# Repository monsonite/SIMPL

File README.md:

# SIMPL

# Introduction.

A serial, interpreted, minimal programming language - adapted for various microcontrollers including Arduino, ARM, MSP430 and experimental FPGA/simulated soft core processors.

SIMPL is intended to be a minimal, human readable scripting language based on the printable ascii character set. 

It provides a serial interface to a microcontroller using easy to remember, single character commands, and a simple interface to sent text strings and numerical output to the screen.

It can be applied to almost any cpu architecture.

# History and Inspiration

It started in 2009 when I required an interactive control method for microcontrollers from a serial terminal.

As a hardware engineer and only an occasional programmer it was driven by the underlying requirements of keeping the onchip resources to an absolute minimum and the interpreter code as simple as possible.

It began with a serial command interpreter for exercising Arduino hardware.

A single uppercase alpha character followed by a numerical parameter, allowed me to step between various routines coded into ROM. 

This was inspired the hex-monitor/debug programs of the mid-1970s to 1980s where uppercase characters followed by a 16-bit address or 8-bit data word allowed you to Examine, Modify and Run programs stored in RAM. 

WozMon on the Apple I was representative of this class of programs. 

https://steckschwein.de/2018/07/22/wozmon-a-memory-monitor-in-256-bytes/ 

A very small interpreter, few commands and tight assembley language programming allowed a useful hex editor in fewer than 256 bytes of code - fitting into a 256byte PROM on the Apple I.  

What started as a variant on a hex monitor has evolved into an interactive language toolkit for exercising a virtual machine VM.

Historical documentation can be found in my blog "Sustainable Suburbia" starting in May 2013: 

http://sustburbia.blogspot.com/2013/05/txtzyme-minimal-interpreter-and.html

At all times I apply the KISS principle - Keep it SIMPL, stupid.

# txtzyme

The breakthrough I needed for what became SIMPL was inspired by Ward Cunningham's Txtzyme nano-interpreter https://github.com/WardCunningham/Txtzyme which I first encountered in May of 2013. I combined Ward's elegant and compact nano-interpreter with my uppercase serial command interpreter.

A compact version of Ward's txtzyme that will run on an ATmega328 Arduino is located here:

https://github.com/monsonite/SIMPL/blob/master/txtzyme_1.ino

It uses 4418 bytes of flash ROM, much of which is attributed to the Arduino I/O functions. 

Many of these can be rewritten for brevity. The baudrate is 115200.

Ward had written a compact interpreter in Arduino C++ which allowed the Arduino's peripheral I/O functions to be accessed using only 13 primitive commands all operating with a 16-bit "register" x :

p print the number contained in x as a 16-bit integer

d define a digital pin

i test the digital pin for input

o set the digital pin either logic 1 or 0

m a millisecond delay

u a microsecond delay

{ start a loop

} end a loop

k read the loop counter

s sample the ADC

_ Print out the text enclosed between the underscored e.g. _Hello World_

h Print out a list of commands and basic help

v Print out the version of the mcu

An early version of Ward's Txtzyme interpreter can be seen here - only about 100 lines of C code:

https://github.com/WardCunningham/Txtzyme/blob/master/Arduinozyme/Arduinozyme.ino

It immediately became apparent that Ward had created the REPL in 2 simple routines contained within the main loop:

txtRead - If serial character present, put it into next location of a serial input buffer - until CRLF pressed

txtEval - Take character from input buffer, identify using switch-case structure and perform action. Loop back to txtRead

It was obvious that by extending the switch-case statement within txtEval, that many more commands could be added. So I added maths, logic and comparison operations and a second variable "y". For example:

123 456 + p       // Put 123 in x, 456 in y, ADD them together in x and print out x followed by a CRLF

Maths operators + - * and / and logical operations & | ^ and ~ were added at this time.

I then started thinking about conditional execution.  Ward had already provided an example of how a snippet of code would be conditionally executed depending on whether a port pin was read as 0 or 1. 

This made ingenious use of his loop structure - code enclosed between braces {........}

9{........}   Repeat the enclosed code 9 times

1{........}   Execute the enclosed code once

0{........}   Skip the enclosed code

An unexpended bonus of this was that comments could be added using a comment in braces preceded by a zero:

0{ This is a comment that will be ignored by interpreter }

Any operation that results in x being 1 or 0 can be used to determine whether the enclosed code is executed or not.

This allowed a simple mechanism for the comparison operators:

Less than <

Equal to =

Greater than >

# Extensibility

Having come from a Forth background, I was familiar how Forth can be extended with new user functions using the "Colon Definition"

Forth uses a dictionary structure and a dictionary look-up to find the location of the code to execute for a particular function. I decided that this could be massively simplified, by restricting the user to only 26 user functions, allocated to the uppercase characters A-Z.

The second big breakthrough was realising that I could point the interpreter to any address in RAM, and not just the input buffer, and have it execute the ascii-based code located there. This gave a simple mechanism for users to write their own SIMPL code into RAM.

You can effectively point the txtEval function to any buffer in memory and it will execute the virtual commands found there until it finds a CRLF.

# Other Influences      

SIMPL builds upon Ward's philosopy of keeping things simple, but adds significantly more functionality and provides the means to make a user extensible language.

SIMPL was also heavily influenced by Charles H. Moore's Forth. It uses the same reverse polish notation RPN,  placing the operands on the stack before executing the operator function.

SIMPL has it's roots in the first electronic computers of the late 1940s where the instruction set was based on uppercase alphabetic characters read from a teletype paper tape into memory. Teletype character sets were limited to uppercase alpha characters, numerals and a few punctuation symbols.

Each character was chosen to have a strong mnemonic value so that it was easily remembered, and made code listings easier to read and write - with fewer mistakes. 

See the Cambridge EDSAC from 1948 for examples of an alpha character instruction set:  https://www.cl.cam.ac.uk/~mr10/Edsac/edsacposter.pdf

SIMPL has evolved as a human readable pseudo-language to control a 16-bit virtual machine based on a Minimal Instruction Set Computer (MISC). If the interpreter is written in C it is easily extended to accommodate 32-bit words.

SIMPL performs the Read-Eval-Print Loop (REPL) required by a serial interpreter shell.  

A MISC is a computer architecture typically defined by a very small instruction set - often with only 8 to 32 instructions. 

One example is the PDP-8, a 12-bit machine from 1965 which had 8 primitive instructions plus the means to control operations on it's accumulator by directly decoding the bitfield from the instruction word. Despite the lack of instructions, the PDP-8 was a versatile machine with it's hardware deficiencies being made up for in software macros.

Additionally, new User functions can be built up by concatenating exisisting functions - this makes SIMPL extensible.

Unlike Forth, there is no dictionary and this avoids the overheads of additional parsing and dictionary searches. SIMPL can be written in about 2kbytes or less, whereas Forth may require 6k bytes. This makes it quicker and easier to port to the assembly language of an unfamiliar microcontroller.

The use of single ascii character commands means that a function can be executed with nothing more than a table look-up to obtain an execution address.

SIMPL is effectively a human readable language for implementing a 16-bit Von Neumann virtual machine on top of the native assembly language of the cpu.

It can be applied to any resource limited processor, it is easier to read and write than assembler but not as complex as a full Forth implementation. 

# Functionality.

SIMPL sets up a minimal serial shell which allows you to control a microcontroller from a few ascii characters typed from a serial terminal.

Numbers 0-9  are processed as a 16-bit integer and used as numerical input (literals) or as control parameters

lowercase alpha a-z  Usually used to access a predefined routine stored in ROM  eg. p is printnumber, u is microsecond delay

Uppercase alpha A-Z  Frequently used to define User Commands or parameters, created to meet the requirements of the application

Symbols Used for arithmetic, logic, loop control and program flow purposes.

This convention is suggested as it gives each character a strong mnemonic value and makes the code more readable. However any of the 96 printable ascii characters could be used to initiate any function in code.

Each ascii character acts as an instruction for a command, forcing a jump to a routine that executes the command, before returning to the interpreter to process the next serial character.

The code required to do this is very straightforward and can be implemented as a large switch-case statement or look up table contained within a while loop.

The serial interpreter was first conceived as a means to access and control the Arduino language functions from a serial link, such as digitalWrite, digitalRead, analog, delay, delaymicroseconds, serialPrint etc.

Later arithmetic, logical, looping and program flow operations were added to extend the functionality.

I describe it as a toolkit, because it has the means to customise it to your own application. Every ascii character, except numerals is treated as a bytecode command. Numeric strings are converted into 16-bit intergers and placed on the stack. They are used as parameters to control the operation of the command.  

For example 1000m will invoke a delay of 1000 milliseconds - ideal for timing operations, flashing LEDs, generating audio tones etc.

SIMPL appears as a series of short ascii phrases For example:

Make a LED on pin 13 flash 10 times, 100mS on and 1000mS off - just 20 characters terminated by a CRLF

13d10{1o100m0o1000m}

13d  - select digital pin 13

10{  - set the loop counter to 10 and begin the loop

1o   - output 1 (HIGH) to the selected pin

100m - delay for 100 milliseconds

0o   - output 0 (LOW) to the pin

1000m  delay for 1000 milliseconds

}    - loop back to the beginning until the loop counter = 0

If you want to keep this code snippet, you can allocate it to a User Command, normally an uppercase character A-Z. Here we use F for flash

:F13d10{1o100m0o1000m}

Every time you type F the mcu will flash the LED 10 times. The code behind F can be redefined at any time to change the flash behaviour

FFFF will execute the code 4 times - flashing the LED 40 times.

# Further Thoughts

SIMPL code is very compact. A lot can be performed using short snippets, taking up very small memory resources. It is the equivalent of a programming "Shorthand" - designed to be quick and concise but still remain human readable.

Most User Definitions are going to be fewer than 32 characters long. A source code editor could be implemented easily using a 40 character x 25 row screen of text.

It gives you the ability to define your own instuction set to suit your application - whether you want to exercise hardware to flash a few LEDs or control an X-Y positioning system.

Scripted commands can be typed in directly followed by a CRLF, or you can send a sequence of commands line by line from a text file, using the Send File option on your terminal programme. 

SIMPL is a minimalist shell to help bring up new microcontroller hardware. The code can be written in C or in assembly language if you require a more compact solution.

SIMPL has been influenced by Forth by putting the numerical parameters on the stack prior to executing the function. However it has removed the complexity of creating a dictionary and parsing and looking up multi character commands. Every valid ascii character is treated as a jump to an action routine, before returning back to the interpreter.

The later versions of SIMPL are self-hosting - you can define your own language to match the requirements of your application.

SIMPL normally uses between 1024 and 2048 bytes of flash ROM to implement. It has been ported to a small MSP430 with only 512 bytes of RAM.

Most of the SIMPL development was done using the Arduino IDE and a compatible microcontroller.

The SIMPL interpreter is about 300 lines of C code that allow you to control the peripherals of a microcontroller from a serial terminal connection.

It enables interaction with the hardware and peripherals using a set of serial commands - for example typing 13h will set digital pin 13 high and typing 13l will set it low. 

There are commands to access the ADC channels, perform integer arithmetic and print numerical results and strings to the terminal.

SIMPL uses single ascii characters as commands to control the hardware - and commands can be strung together to make new commands - a litte bit like FORTH.

There are 96 printable ascii characters, but omitting numbers 0-9 and backspace limits SIMPL to 85 unique commands.

A SIMPL interpreter shell can be written in about 300 bytes of assembly language. In addition to this are the function routines - so a typical implementation is about 1k to 2k bytes of ROM. 

The shell can also be written in C, or using the Arduino C++ language - but the ROM size will be significantly larger. Many of the Arduino reference language functions use a significant amount of ROM.

# Implementation.

SIMPL can be created from half a dozen basic function routines. These implement the Read-Eval-Print Loop REPL

getchar - get the next character from the text input buffer

putchar - send a character to the terminal

number  - parse a string of numerical characters until a non-numeric character (eg space) convert the string to a 16-bit input and put it on the stack

printnumber - output a 16-bit integer to the serial terminal in the form of a decimal numeric string

lookup  - use the value of the ascii character to index into a lookup table or switch-case structure.

Obtain the Code Field Address(CFA) associated with that character.
      
Jump to and execute the code at the CFA. Jump to next at the end of the function code
          
next      Read the next serial character and process it.          

The underlying philosophy of SIMPL is to make the "mechanics" of the interpreter as simple as possible, and to keep the bytecount as low as possible.

The means that it is relatively easy to port from one mcu to another.

SIMPL has been used as a "bring-up" language for a number of mcus - including ATmega, MSP430, ARM Cortex M0, M4, M7.

It has also been used to explore and exercise new microcontroller architectures that have been created as software simulations.

; Serial Interpreted Microcontroller Programming Language

;-------------------------------------------------------------------------------

; SIMPL - a very small Forth Inspired Extensible Language 

; Type ? to get list of commands

; Type H or M to get a test message

; Ken Boak   May to September 2017

; Loops, I/O, Strings and Delays added

Here are some quick instructions - it uses lower case commands usually preceded by an integer number 65536 max

p      print out the number on the top of the stack followed by a carriage return

1234p   Print the number 1234

14sp    Take an ADC sample from pin 14 and print it as an integer

_Hello World_   Print the text string contained between the underscores

47d     Define the GPIO pin to be used for input or output

1o      Output logic 1 to the previously defined output pin

0o      Output logic 0 to the previously defined output pin

1000m   A delay of 1000 milliseconds

100u    A delay of 100 microseconds

b       Print the current value of the millisecond counter - useful for timing how long functions take

c       Print the current valule of the microsecond counter - useful for timing how long functions take

{ }     Create a loop structure

k       The current value of the loop counter - decrements each time around the loop

10{kp}   Print out the value of the loop counter as it decrements

Make a LED on pin 47 flash 10 times

47d10{1o100m0o100m}

1o and 0o can be replaced with h and l (HIGH and LOW)

47d10{h100ml1000m}

47dl Initially set LED pin low

10{h200ml200m}      Flash the LED 10 times  200mS on, 1200mS off

Audio Tones, connect a small speaker to the output pin - use u the microsecond delay function

1000{1o250u0o250u}  Create a short audio tone on pin 47

100{14sp}    Take 100 ADC samples on pin 14 (AN0) and print them out

10 11+p      Add 10 and 11 and print the result

Maths operators +  - * and / are recognised

Logic operators & | ^ and ~  (AND OR XOR NOT) are recognised

;		Upper case letters are used to define Users "words"

;		User Routines are defined by capital letters starting  with colon : and end with semicolon ;

;		eg  :F10(100mh200ml);		;	Flash the led 10 times - high for 100mS and low for 200mS

;		You can play sequences of notes through a small speaker  ABC etc

;   :A40{h1106ul1106u);		       musical note A

;   :B5{h986ul986u);			 musical note B

;   :C51{h929ul929u);			 musical note C

;   :D57{h825ul825u);			 musical note D

;   :E64{h733ul733u);			 musical note E

;   :F72{h690ul691u);			 musical note F

;   :G81{h613ul613u);			 musical note G

;   :H_Hello World, and welcome to SIMPL_;   A Banner Message

;   Examples of SIMPL phrases

;   eg add 123 and 456 and print the result to the terminal

;   123 456+p

;   Loop 10 times printing "Spurs are Fab!" Curley brackets { and } are used to enclose the code to be repeated within the loop

;   The number outside the opening brace is the loopcounter. The contents of the loop will be executed until the loopcounter is decremented to zero  

;   10{_Spurs are Fab!_}

;   Flash a LED 10 times 100mS on 200mS off

;   10{h100ml200m}

;   Toggle a port pin at 1MHz   1000{hlhlhlhlhlhlhlhlhlhl}

;--------------------------------__LIST OF CHARACTERS, FUNCTIONS AND OPERATORS__-----------------------------------------------

;	Lower case letters are used for more complex inbuilt commands executed from ROM. Here are some suggestions - but not extensive

; a

; b      print the milliseconds counter - for timing durations

; c      print the microseconds counter

; d      Define a digital I/O pin

; e

; f

; g

; h       set port pin high

; i       input byte from port

; j

; k       access the loop counter variable

; l       set port pin low

; m       milliseconds delay

; n       Ouput an 8-bit binary number on 8 consecutive port pins

; o       output bit to port

; p       print the top of stack to terminal

; q       print the ascii character at given RAM location

; r       read input pin

; s       sample the ADC

; t       Toggle a port pin - equivalent to {hl}

; u       microseconds delay

; v

; w

; x       Three registers that form a stack

; y       Three registers that form a stack

; z       Three registers that form a stack

;         Sybolic Operators

; +       ADD

; -       SUB

; *       MUL

; /       DIV

; &       AND

; |       OR

; ^       XOR

; ~       NOT INVert

; @       Fetch

; !       Store

; "       Stack operation DUP

; '       Stack operation DROP

; $       Stack operation SWAP

; %       Stack operation OVER

; :       Start colon definition

; ;       End colon definition

; #       16-bit literal

; <       LESS than

; =       EQUAL

; >       GREATER than

; \       Comment   \This is a comment

; ,       Array separator

; .       Print top of stack (same as p)

;         Conditional code

; (       Start an array separated by commas

; )       End of array

; {       Start a Loop

; }       End of Loop

; Start a switch-case [

; End a switch-case   ]

; _Hello World_       Print a text string enclosed inside the underscores

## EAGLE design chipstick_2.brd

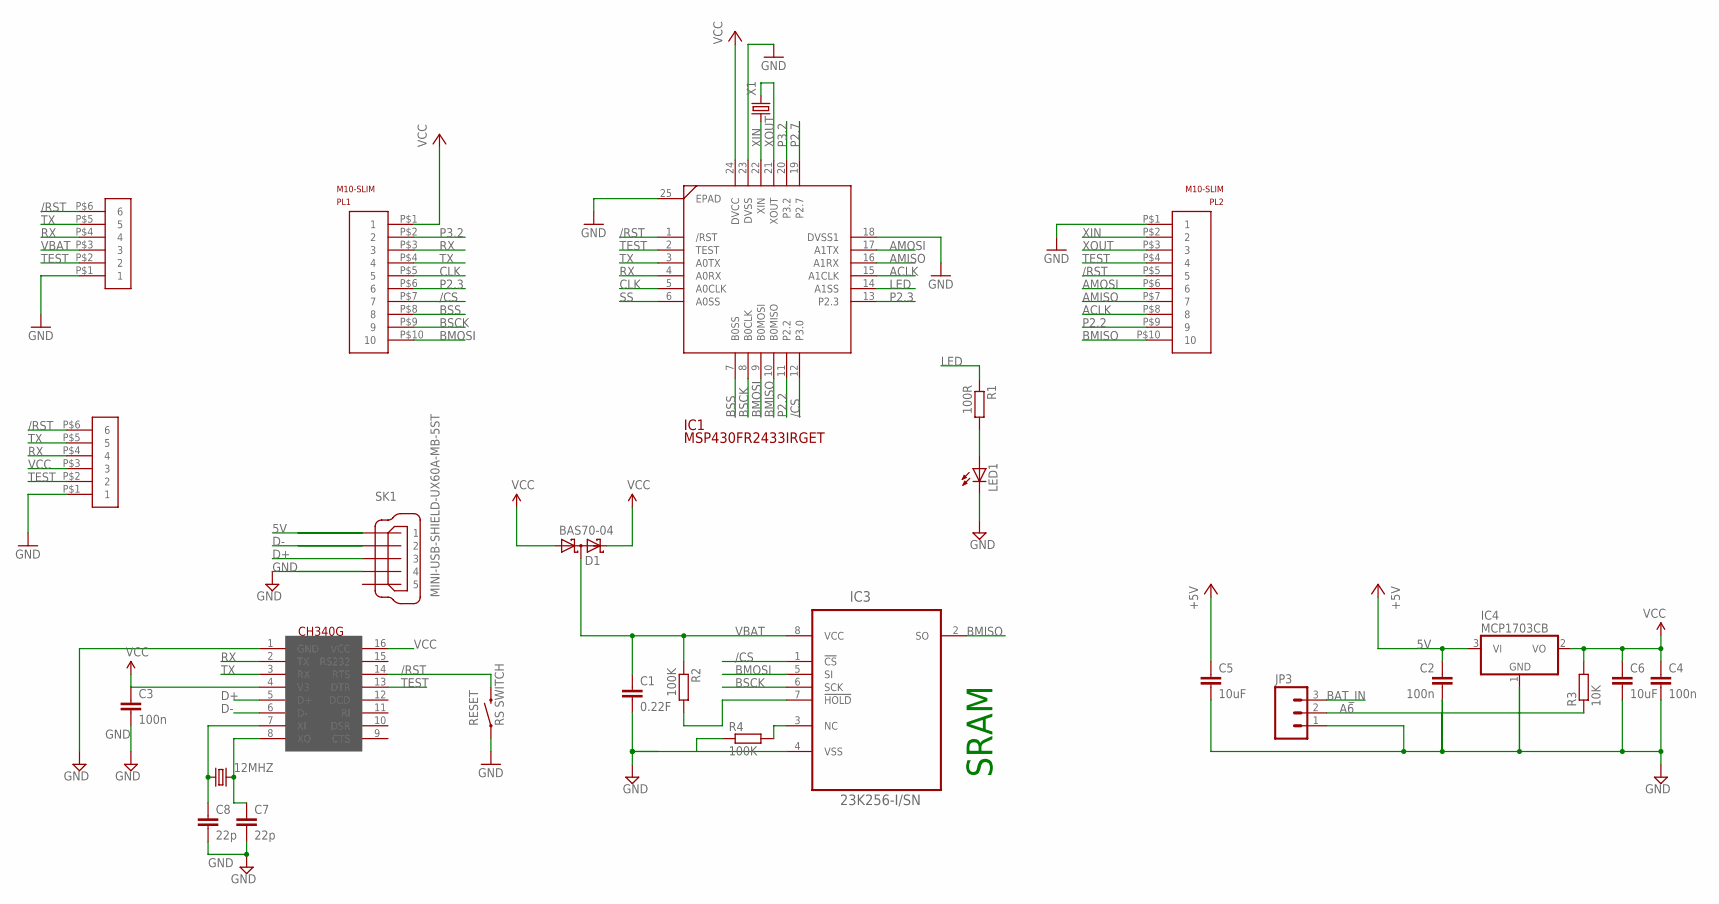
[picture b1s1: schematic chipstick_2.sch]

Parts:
12MHZ: CRYSTALCTS406; CTS406
C1: 0.22F; C5B5.5
C2, C3, C4: 100n; C0603
C5, C6: 10uF; C0603
C7, C8: 22p; C0603
D1: BAS70-04; SOT23
IC1: MSP430FR2433IRGET; QFN50P400X400X100-25N
IC2: CH340G; SOIC16
IC3: 23K256-I/SN; SOIC127P600X175-8N
IC4: MCP1703CB; SOT23
JP1, JP2: 1X06-1.27MM
JP3: M03POLAR; MOLEX-1X3
LED1: LED0603; LED-0603
PL1, PL2: M10-SLIM
R1: 100R; R0603
R2, R4: 100K; R0402
R3: 10K; R0603
RESET: RS SWITCH; TACTILE-SWITCH-1101NE
SK1: MINI-USB-SHIELD-UX60A-MB-5ST; UX60A-MB-5ST
X1: CRYSTALTC26V; TC26V

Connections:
5V: C2.1, C5.1, IC4.3 (VI), SK1.1
/CS: IC1.12 (P3.0), IC3.1 (!CS), PL1.P$7 (7)
/RST: IC1.1 (/RST), IC2.14 (RTS), JP1.P$6 (6), JP2.P$6 (6), PL2.P$5 (5), RESET.2
A6: JP3.2, R3.1
ACLK: IC1.15 (A1CLK), PL2.P$8 (8)
AMISO: IC1.16 (A1RX), PL2.P$7 (7)
AMOSI: IC1.17 (A1TX), PL2.P$6 (6)
BAT_IN: JP3.3
BMISO: IC1.10 (B0MISO), IC3.2 (SO), PL2.P$10 (10)
BMOSI: IC1.9 (B0MOSI), IC3.5 (SI), PL1.P$10 (10)
BSCK: IC1.8 (B0CLK), IC3.6 (SCK), PL1.P$9 (9)
BSS: IC1.7 (B0SS), PL1.P$8 (8)
CLK: IC1.5 (A0CLK), PL1.P$5 (5)
D+: IC2.5 (D+), SK1.3
D-: IC2.6 (D-), SK1.2
GND: C1.2, C2.2, C3.2, C4.2, C5.2, C6.2, C7.2, C8.2, IC1.18 (DVSS1), IC1.23 (DVSS), IC1.25 (EPAD), IC2.1 (GND), IC3.4 (VSS), IC4.1 (GND), JP1.P$1 (1), JP2.P$1 (1), JP3.1, LED1.C, PL2.P$1 (1), R4.1, RESET.1, SK1.4
LED: IC1.14 (A1SS), R1.1
unnamed: IC3.3 (NC), R4.2
unnamed: 12MHZ.1, C8.1, IC2.7 (XI)
unnamed: 12MHZ.3 (2), C7.1, IC2.8 (XO)
unnamed: LED1.A, R1.2
unnamed: IC3.7 (!HOLD), R2.2
P2.2: IC1.11 (P2.2), PL2.P$9 (9)
P2.3: IC1.13 (P2.3), PL1.P$6 (6)
P2.7: IC1.19 (P2.7)
P3.2: IC1.20 (P3.2), PL1.P$2 (2)
RX: IC1.4 (A0RX), IC2.2 (TX), JP1.P$4 (4), JP2.P$4 (4), PL1.P$3 (3)
SS: IC1.6 (A0SS)
TEST: IC1.2 (TEST), IC2.13 (DTR), JP1.P$2 (2), JP2.P$2 (2), PL2.P$4 (4)
TX: IC1.3 (A0TX), IC2.3 (RX), JP1.P$5 (5), JP2.P$5 (5), PL1.P$4 (4)
VBAT: C1.1, D1.3 (C1A2), IC3.8 (VCC), JP2.P$3 (3), R2.1
VCC: C3.1, C4.1, C6.1, D1.1 (A1), D1.2 (C2), IC1.24 (DVCC), IC2.4 (V3), IC2.16 (VCC), IC4.2 (VO), JP1.P$3 (3), PL1.P$1 (1), R3.2
XIN: IC1.22 (XIN), PL2.P$2 (2), X1.1
XOUT: IC1.21 (XOUT), PL2.P$3 (3), X1.2

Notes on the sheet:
SRAM

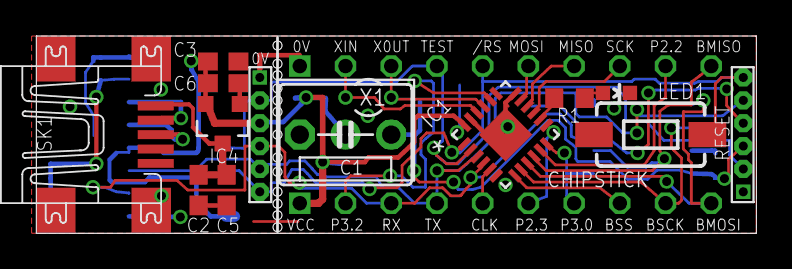
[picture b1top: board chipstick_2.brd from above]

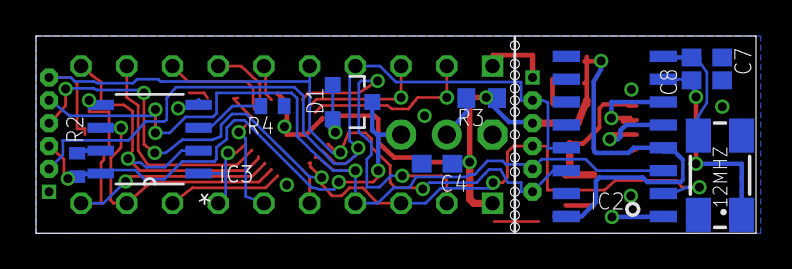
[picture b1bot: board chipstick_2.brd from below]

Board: 2 copper layers, 40.0 x 11.0 mm, 27 parts (10 on the bottom side), 31 nets.

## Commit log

2016-03-22 Added files via upload
    This is SIMPL for the MSP430FR4133 LaunchPad - programmed using Energia
2016-03-23 Added files via upload
2016-03-28 Added files via upload
    SIMPLEX V2.11 adds support for tthe 23LC1024 128Kx8 static RAM
    Commands a, b, c, d, e, f & g are used to exercise the external RAM
    a = just a placeholder for future assembler
    b Block Load
    c Placeholder for future compile option
    d Block Dump of 1024 bytes default
2016-03-29 Added files via upload
    Add musical tones, support for 7 LEDs, accurate timing and general tidy-up
2017-09-22 Add files via upload
    This is SIMPL running under Arduino on the STM32L433 on the BlackIce board
2017-10-15 Add files via upload
    An assembler framework using SIMPL Oct 15 2017
2017-12-04 Create SIMPL_2433_ASM
    First draft of SIMPL ported in assembly language to MSP430FR2443 LaunchPad
2021-01-10 Add files via upload
    Version for Arduino Duemilenove
2021-01-12 Add files via upload
    Original Arduino version of txtzyme Flash: 4418 bytes 115200 baud
2021-01-12 Add files via upload
    SIMPL for MSP430G2553 by Zhe Hu 31-08-2019
2021-01-23 Add files via upload
    32-bit SIMPL framework for Arduino Uno

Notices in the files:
parts and their libraries:
SparkFun-Connectors: Licensing: Creative Commons ShareAlike 4.0 International - https://creativecommons.org/licenses/by-sa/4.0
